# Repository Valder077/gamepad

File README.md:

# Suhansh's Hackpad
## Description 
This is my personal take on a macropad, catered for the games I play, which include Fortnite and Valorant, featuring WASD keys and a dedicated button(crouching or anything you want to be honest). It also includes a rotary encoder that adjusts the system's volume, providing quick audio control, in the minimalistic set up which is compact and functional, hence enhancing my personal gaming experience. 

## Schematic
This is my schematic

## PCB
This is my PCB that i designed in KiCad

## Case Assembly 
This is my case assembly 

## BOM
- 5x MX-Style switches
- 5x DSA keycaps
- 1x EC11 Rotary encoder
- 4x M3x5mx4mm heatset inserts
- 4x M3x16mm screws
- 1x XIAO RP2040
- 1x case (with 2 printed parts)

## Challenges
I think they key challenge with building this macropad was the fact that I am new to hardware so the entire process of building this took quite a lot of googling and asking around for help but I am proud of where this project ended up.

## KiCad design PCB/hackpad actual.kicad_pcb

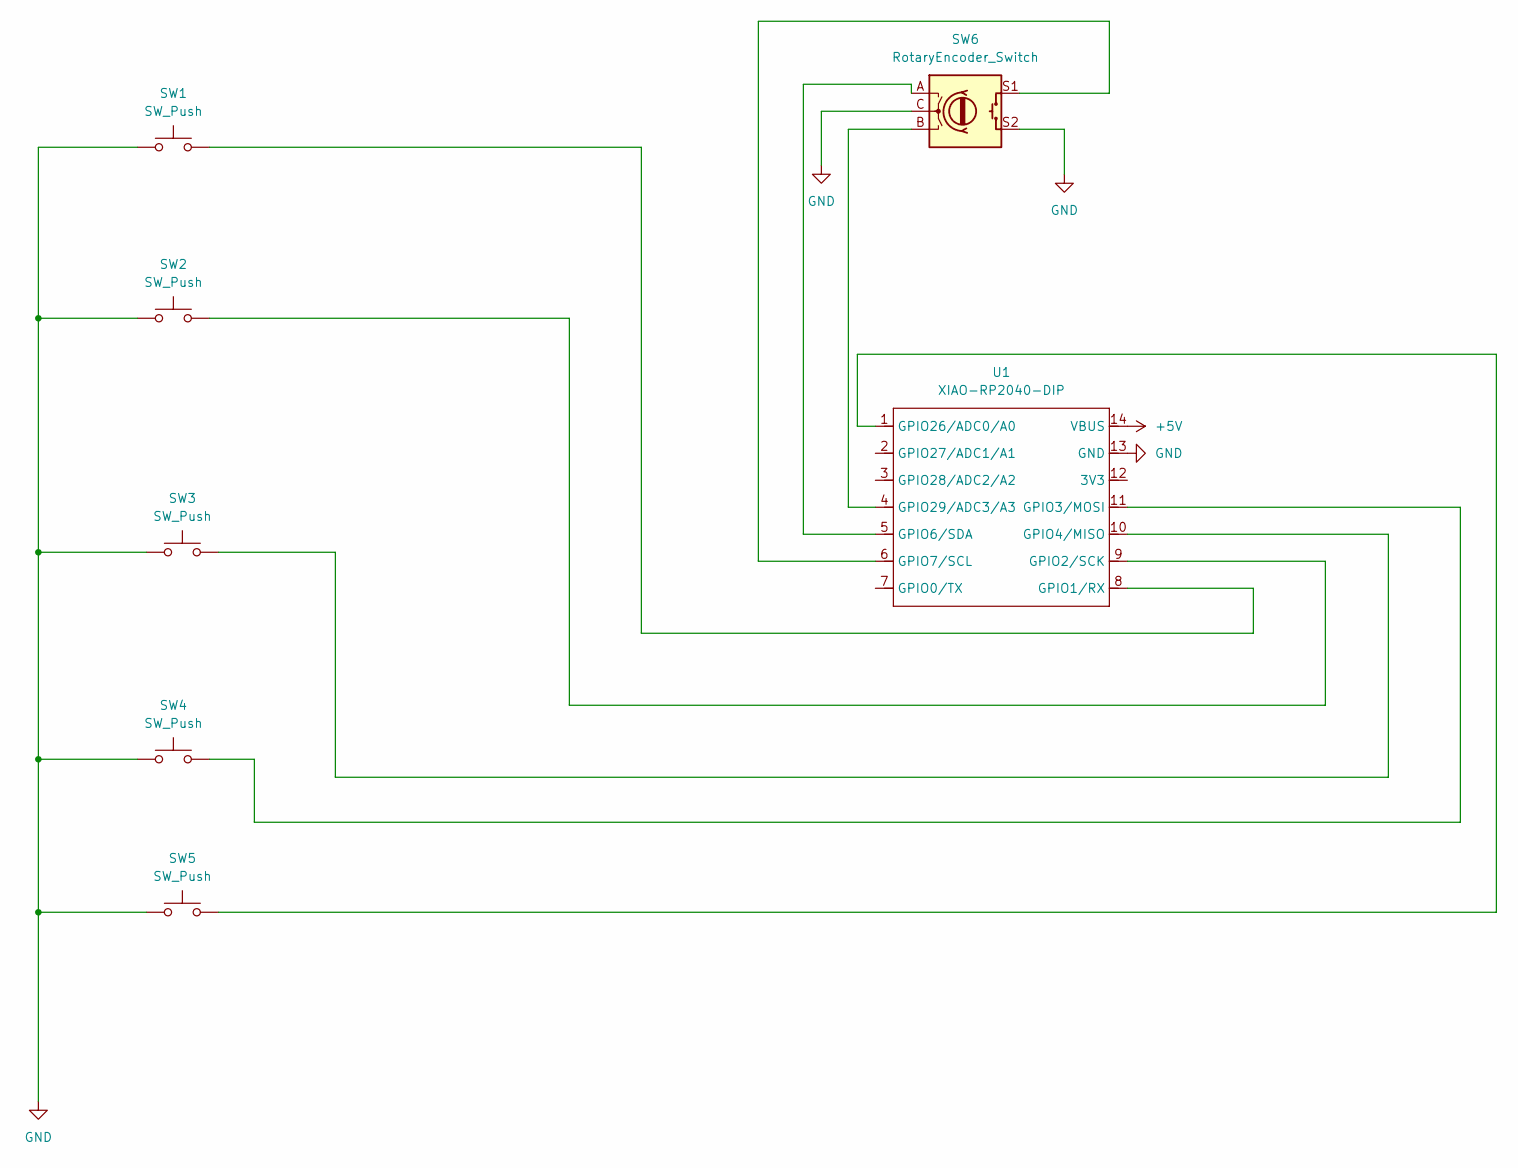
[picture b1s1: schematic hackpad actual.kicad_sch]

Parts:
SW1, SW2, SW3, SW4, SW5: SW_Push; SW_Cherry_MX_1.00u_PCB
SW6: RotaryEncoder_Switch; RotaryEncoder_Alps_EC11E-Switch_Vertical_H20mm
U1: XIAO-RP2040-DIP

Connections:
+5V: U1.14 (VBUS)
GND: SW1.1, SW2.1, SW3.1, SW4.1, SW5.1, SW6.C, SW6.S2, U1.13 (GND)
unnamed: SW1.2, U1.8 (GPIO1/RX)
unnamed: SW2.2, U1.9 (GPIO2/SCK)
unnamed: SW4.2, U1.11 (GPIO3/MOSI)
unnamed: SW3.2, U1.10 (GPIO4/MISO)
unnamed: SW6.A, U1.5 (GPIO6/SDA)
unnamed: SW6.S1, U1.6 (GPIO7/SCL)
unnamed: SW5.2, U1.1 (GPIO26/ADC0/A0)
unnamed: SW6.B, U1.4 (GPIO29/ADC3/A3)

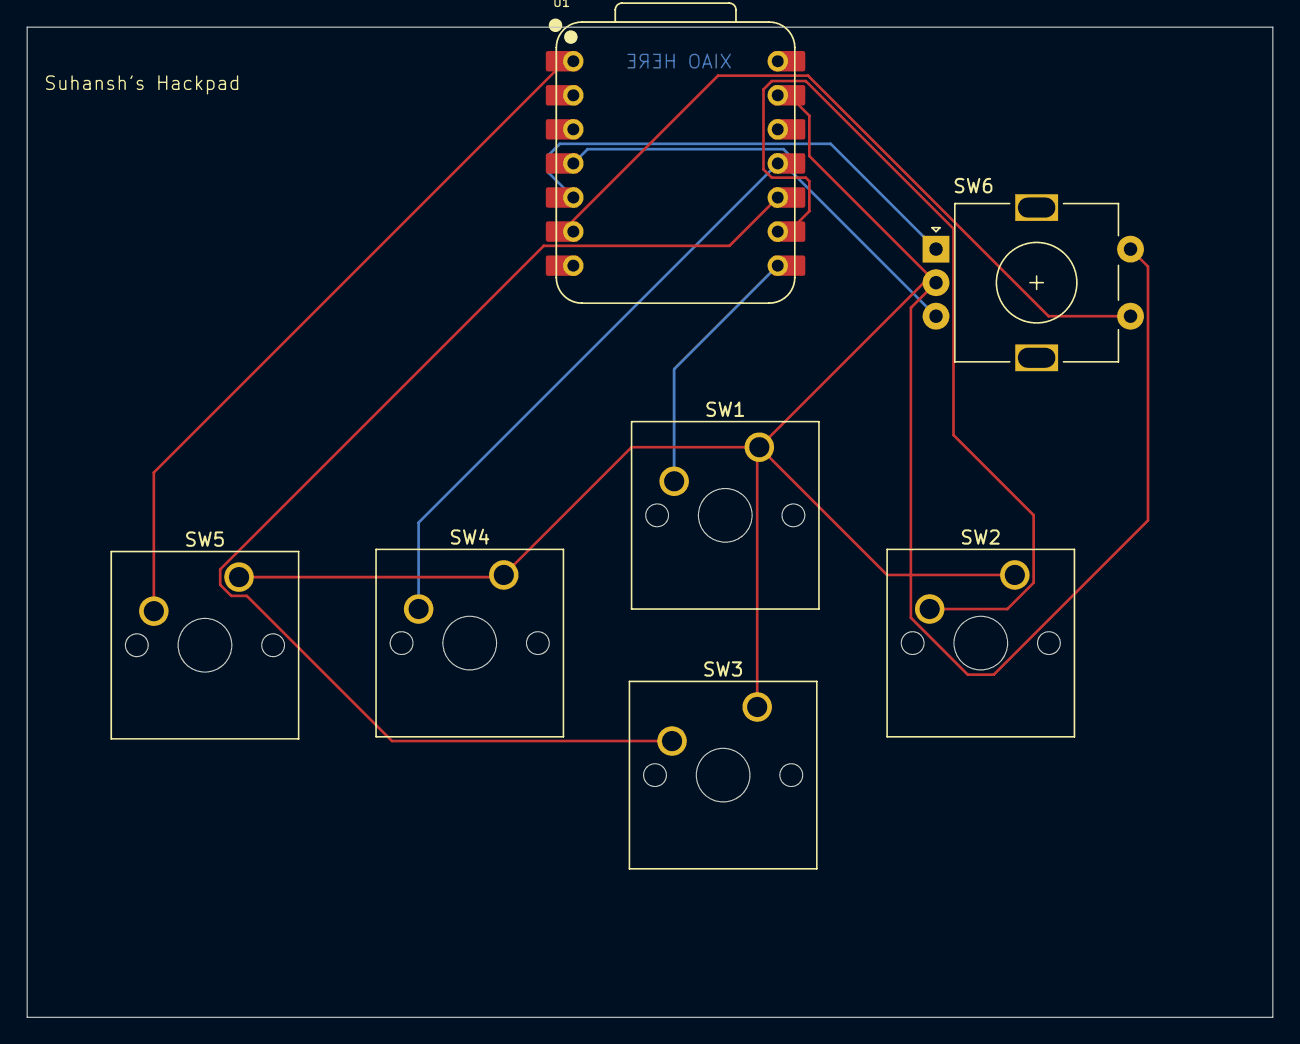
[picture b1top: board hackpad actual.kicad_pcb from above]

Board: 2 copper layers, 92.9 x 73.8 mm, 7 parts (0 on the bottom side), 9 nets.

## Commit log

2025-07-05 links typo
2025-07-05 minor edits
2025-07-05 more edits
2025-07-08 rereview edits
2025-07-08 typos
2025-07-08 typo again
